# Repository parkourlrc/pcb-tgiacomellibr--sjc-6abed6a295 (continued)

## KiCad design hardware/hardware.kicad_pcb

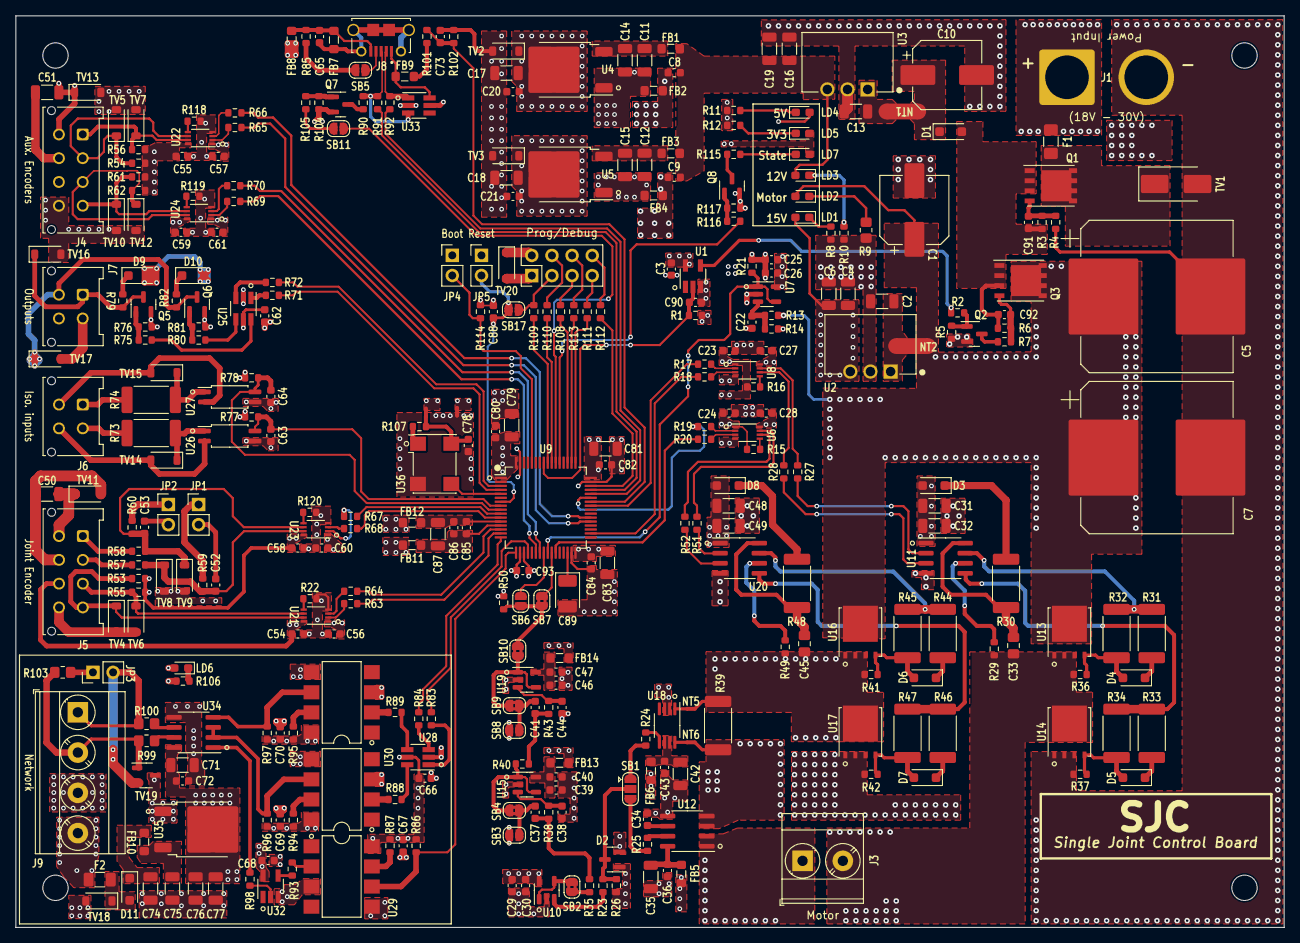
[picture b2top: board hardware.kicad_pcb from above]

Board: 4 copper layers, 160.0 x 115.0 mm, 346 parts (0 on the bottom side), 216 nets.

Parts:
C1, C10: 47uF 63V 20%; CP_Elec_8x10.5
C2, C6, C11, C12, C13, C17, C18, C19, C31, C35, C42, C48, C75, C76, C79: 10uF 10% 50V; C_1206_3216Metric
C3, C8, C9, C20, C21, C23, C24, C25, C27, C28, C29, C36, C39, C43, C46, C54, C55, C56, C57, C58, C59, C60, C61, C62, C65, C66, C67, C68, C69, C70, C72, C73, C78, C80, C82, C84, C86, C88, C93: 100nF 5% 50V; C_0603_1608Metric
C4, C16: 22uF 10% 25V; C_1206_3216Metric
C5, C7: 680uF 63V 20%; CP_Elec_18x17.5
C14, C15, C32, C49, C50, C51, C71, C74, C77, C81, C83, C87: 1uF 10% 50V; C_1206_3216Metric
C22: 12nF 5% 50V; C_0603_1608Metric
C26, C30, C40, C47, C63, C64, C85, C90, C91, C92: 10nF 5% 50V; C_0603_1608Metric
C33, C45: 82nF 5% 50V; C_0805_2012Metric_Pad1.18x1.45mm_HandSolder
C34, C52, C53: 22nF 5% 50V; C_0603_1608Metric
C37, C38, C41, C44: 39nF 5% 50V; C_0603_1608Metric
C89: 4.7uF 10% 20V; CP_EIA-3528-15_AVX-H_Pad1.50x2.35mm_HandSolder
D1, D3, D8, D11: PMEG60T20ELR; D_SOD-123F
D2: BAT54S; SOT-23
D4, D5, D6, D7, D9, D10: PMEG60T10ELR; D_SOD-123F
F1: 25A 32V; Fuse_1206_3216Metric_Pad1.42x1.75mm_HandSolder
F2: 60V 100mA; Fuse_1206_3216Metric
FB1, FB2, FB3, FB4, FB5, FB6, FB7, FB8, FB9, FB10, FB11, FB12, FB13, FB14: 220R 3A; L_0805_2012Metric_Pad1.05x1.20mm_HandSolder
H1, H2, H3, H4: MountingHole; MountingHole_3.2mm_M3_ISO7380
J1: V_{POWER}; SolderWire-16.8sqmm_1x02_P10.0mm_D5.5mm_OD7.0mm
J3: Motor; TerminalBlock_Phoenix_MKDS-3-2-5.08_1x02_P5.08mm_Horizontal
J4: Aux. encoders; Molex_Micro-Fit_3.0_43045-0812_2x04_P3.00mm_Vertical
J5: Joint encoders; Molex_Micro-Fit_3.0_43045-0812_2x04_P3.00mm_Vertical
J6: Isolated Inputs; Molex_Micro-Fit_3.0_43045-0412_2x02_P3.00mm_Vertical
J7: Outputs; Molex_Micro-Fit_3.0_43045-0412_2x02_P3.00mm_Vertical
J8: AMPHENOL_10118194-0001LF
J9: RS-485; TerminalBlock_Phoenix_MKDS-3-4-5.08_1x04_P5.08mm_Horizontal
J10: PROG_{DBG}; PinHeader_2x04_P2.54mm_Vertical
JP1, JP2, JP4, JP5: E-STOP_DIV; PinHeader_1x02_P2.54mm_Vertical
JP3: RS-485 TERM; PinHeader_1x02_P2.54mm_Vertical
LD1, LD2, LD3, LD4, LD5, LD6, LD7: 1.8V @ 5mA; LED_0603_1608Metric_Pad1.05x0.95mm_HandSolder
NT1, NT2: PWR-DRV; NetTie-2_SMD_Pad2.0mm
NT3: 3V3_OSC; NetTie-2_SMD_Pad0.5mm
NT4: GND_OSC; NetTie-2_SMD_Pad0.5mm
NT5: SHUNT IN-; NetTie-2_SMD_Pad0.5mm
NT6: SHUNT IN+; NetTie-2_SMD_Pad0.5mm
Q1, Q3: SI7149ADP; PowerPAK_SO-8_Single
Q2, Q5, Q6, Q8: NDS7002A; SOT-23
Q7: BSS84; SOT-23
R1, R3, R5, R6, R13, R36, R37, R41, R42, R76, R81, R85, R104, R114, R117: 100k 1%; R_0603_1608Metric
R2, R21, R59, R60, R75, R80, R86, R96, R97, R105, R116: 1k 1%; R_0603_1608Metric
R4, R7, R102: 82k 0.1%; R_0603_1608Metric
R8, R15, R16, R22, R53, R54, R55, R56, R61, R62, R87, R94, R95, R118, R119, R120: 2k7 1%; R_0603_1608Metric
R9: 5.62k 5% 250mW; R_0805_2012Metric_Pad1.20x1.40mm_HandSolder
R10, R77, R78, R79, R82: 2k 5%; R_0603_1608Metric
R11: 680R 1%; R_0603_1608Metric
R12, R106, R115: 330R 1%; R_0603_1608Metric
R14, R23, R107: 10k 1%; R_0603_1608Metric
R17, R18, R19, R20, R27, R28, R51, R52, R63, R64, R65, R66, R67, R68, R69, R70, R71, R72, R83, R84, R98, R108, R109, R110, R111, R112, R113: 33R 1%; R_0603_1608Metric
R24: 270R 0.1%; R_0603_1608Metric
R25: 510R 0.1%; R_0603_1608Metric
R26, R35, R38, R40, R43, R50: 1.02k 0.1%; R_0603_1608Metric
R29, R49: 0R; R_0603_1608Metric
R30, R48: 2R 5% 2W; R_2512_6332Metric_Pad1.40x3.35mm_HandSolder
R31, R33, R44, R46: 2.4R 1% 1W; R_2512_6332Metric_Pad1.40x3.35mm_HandSolder
R32, R34, R45, R47: 130R 1% 1W; R_2512_6332Metric_Pad1.40x3.35mm_HandSolder
R39: 8mR 1% 2W; R_2512_6332Metric_Pad1.40x3.35mm_HandSolder
R57, R58, R90: 1.5k 1%; R_0603_1608Metric
R73, R74: 1.6k 5% 1W; R_2512_6332Metric_Pad1.40x3.35mm_HandSolder
R88, R89, R93: 160R 5% 1/8W; R_0603_1608Metric
R91, R92: 22R 1%; R_0603_1608Metric
R99, R100: 10R 1% 1/2W; R_0805_2012Metric_Pad1.20x1.40mm_HandSolder
R101: 47k 0.1%; R_0603_1608Metric
R103: 120R 0.1% 1/8W; R_0805_2012Metric_Pad1.20x1.40mm_HandSolder
SB1: CS_SEL; SolderJumper-3_P1.3mm_Open_RoundedPad1.0x1.5mm
SB2, SB4, SB7, SB9, SB10: SolderJumper-2_P1.3mm_Bridged2Bar_RoundedPad1.0x1.5mm
SB3, SB5, SB6, SB8, SB11, SB17: SolderJumper-2_P1.3mm_Open_RoundedPad1.0x1.5mm
TV1: SMBJ30A; D_SMB_Handsoldering
TV2, TV5, TV7, TV8, TV9, TV10, TV12, TV13: PTVS5V0S1UR; D_SOD-123
TV3, TV20: PTVS3V3S1UR; D_SOD-123
TV4, TV6, TV11, TV16, TV17, TV18: PTVS12VS1UR; D_SOD-123
TV14, TV15: PTVS30VS1UR; D_SOD-123
TV19: SM712; SOT-23-3
U1, U32: SN74LVC1G04DBVR; SOT-23-5_HandSoldering
U2: VXO78015-1000; CONV_VXO78015-1000
U3: VXO78012-1000; CONV_VXO78012-1000
U4: NCP1117DT50; TO-252-2
U5, U35: NCP1117DT33; TO-252-2
U6, U8, U21, U22, U23, U24: 74LVC2T45DC; VSSOP-8_2.3x2mm_P0.5mm
U7, U10, U15, U19: TLV9051; SOT-23-5
U9: STM32F446RETx; LQFP-64_10x10mm_P0.5mm
U11, U20: FAN7382; SOIC-8_3.9x4.9mm_P1.27mm
U12: ACS712-20A; SOIC-8_3.9x4.9mm_P1.27mm
U13, U14, U16, U17: BSC0902NSI; TDSON-8-1
U18: AD8418; MSOP-8_3x3mm_P0.65mm
U25, U28: SN74LVC2G04; SOT-23-6_Handsoldering
U26, U27: TLP291; SOP-4_4.4x2.6mm_P1.27mm
U29, U30, U31: 6N137; SMDIP-8_W7.62mm
U33: USBLC6-4SC6; SOT-23-6_Handsoldering
U34: SN65HVD75DR; SOIC-8_3.9x4.9mm_P1.27mm
U36: YSO110TR-16MHz; Oscillator_SMD_YXC_YSO110TR_7050-4Pin_7.0x5.0mm

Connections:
+3V3: C3.1, C18.2, C21.2, C23.2, C24.2, C25.1, C26.1, C29.1, C30.1, C56.1, C57.1, C60.2, C61.1, C62.1, C66.1, C67.1, C79.2, C80.2, C81.2, C82.2, C83.2, C84.2, C93.2, D2.2, FB11.1, FB13.2, FB14.2, J10.2, JP4.1, LD5.2 (A), LD7.2 (A), NT3.2, Q7.2 (S), R1.2, R15.2, R16.2, R77.2, R78.2, R86.2, R87.2, R104.2, TV3.1 (K), TV20.1 (K), U1.5 (VCC), U5.2 (VO), U6.1 (VCCA), U7.5 (V+), U8.1 (VCCA), U9.1 (VBAT), U9.19 (VDD), U9.32 (VDD), U9.48 (VDD), U9.64 (VDD), U10.5 (V+), U21.1 (VCCA), U22.1 (VCCA), U23.1 (VCCA), U24.1 (VCCA), U25.5 (V_{CC}), U28.5 (V_{CC}), U29.8 (VCC)
+3V3A: C85.2, C86.2, C87.2, FB11.2, U9.13 (VDDA)
+3V3_ISO: C68.1, C69.1, C70.1, C71.1, C72.1, C76.2, C77.2, LD6.2 (A), R94.2, R95.2, R96.2, R97.2, U30.8 (VCC), U31.8 (VCC), U32.5 (VCC), U34.8 (VCC), U35.2 (VO)
+3V3_OSC: C78.1, NT3.1, R107.2, U36.4 (V_{DD})
+5V: C17.2, C20.2, C27.1, C28.1, C50.2, C51.2, C54.2, C55.2, C58.1, C59.2, D9.2 (A), D10.2 (A), FB5.1, FB6.1, J4.5, J4.7, J5.5, J5.7, LD4.2 (A), R53.2, R54.2, R55.2, R56.2, R61.2, R62.2, TV2.1 (K), TV11.1 (K), TV13.1 (K), U4.2 (VO), U6.8 (VCCB), U8.8 (VCCB), U21.8 (VCCB), U22.8 (VCCB), U23.8 (VCCB), U24.8 (VCCB), U33.5 (VBUS)
+5V_USB: FB9.2, J8.1 (VBUS), U33.6 (I/O4)
+12V: C8.2, C9.2, C16.2, C19.2, FB1.2, FB3.1, LD3.2 (A), U3.3 (+V_{OUT})
+12V_ISO: F2.1, J9.4
+15V: C4.2, C6.2, C31.1, C32.1, C48.2, C49.2, D3.2 (A), D8.2 (A), LD1.2 (A), U2.3 (+V_{OUT}), U11.1 (V_{CC}), U20.1 (V_{CC})
/Communication/+12V_ISO_DC: C74.2, D11.1 (K), FB10.2
/Communication/+12V_ISO_FLT: C75.2, FB10.1, U35.3 (VI)
/Communication/COM_USB_D+: R91.1, U9.45 (PA12)
/Communication/COM_USB_D-: R92.1, U9.44 (PA11)
/Communication/COM_USB_PU: SB11.1 (A), U9.54 (PD2)
/Communication/COM_USB_V_{BUS}_SIG: C73.2, R101.2, R102.2, U9.42 (PA9)
/Communication/ISO_RX: R98.2, U32.2 (A)
/Communication/ISO_TX: R97.1, U31.6 (VO), U34.4 (D)
/Communication/ISO_~RE_DE: R96.1, U30.6 (VO), U34.2 (~RE), U34.3 (DE)
/Communication/RS485+: J9.2, R99.1, R103.1, TV19.1
/Communication/RS485-: J9.1, JP3.2, R100.1, TV19.2
/Communication/RS485_RX: R86.1, U9.17 (PA3), U29.6 (VO)
/Communication/RS485_TX: R84.2, U9.16 (PA2)
/Communication/RS485_~RE_DE: R83.2, U9.20 (PA4)
/Communication/RS+: R99.2, U34.7 (B)
/Communication/RS-: R100.2, U34.6 (A)
/Communication/USB_D+: J8.3 (D+), R90.1, R91.2, U33.3 (I/O2)
/Communication/USB_D-: J8.2 (D-), R92.2, U33.1 (I/O1)
/Communication/USB_DP_PU: Q7.3 (D), R90.2
/Control/AUX1_ENC_CH1: R69.1, U9.22 (PA6)
/Control/AUX1_ENC_CH2: R70.1, U9.23 (PA7)
/Control/AUX2_ENC_CH1: R65.1, U9.37 (PC6)
/Control/AUX2_ENC_CH2: R66.1, U9.38 (PC7)
/Control/BOOT: JP4.2, R114.2, U9.60 (BOOT0)
/Control/CURRENT_SIGNAL_FILT: R50.2, SB6.2 (B), SB7.2 (B), SB10.2 (B)
/Control/DEBUG_USART_TX: R108.1, U9.51 (PC10)
/Control/GP_ISO_IN_A: C63.2, R77.1, U9.8 (PC0), U26.4
/Control/GP_ISO_IN_B: C64.2, R78.1, U9.9 (PC1), U27.4
/Control/GP_OUT_A: R71.2, U9.4 (PC15)
/Control/GP_OUT_B: R72.2, U9.3 (PC14)
/Control/JOINT_ENC_CH1: R64.1, U9.14 (PA0)
/Control/JOINT_ENC_CH2: R63.1, U9.15 (PA1)
/Control/JOINT_SW_L: R67.1, U9.10 (PC2)
/Control/JOINT_SW_R: R68.1, U9.11 (PC3)
/Control/JTCK/SWCLK: R111.1, U9.49 (PA14)
/Control/JTDI: R113.1, U9.50 (PA15)
/Control/JTDO/TRACESWO: R110.1, U9.55 (PB3)
/Control/JTMS/SWDIO: R112.1, U9.46 (PA13)
/Control/L_MOT_HI_{PWM}: R17.2, U9.41 (PA8)
/Control/L_MOT_LO_{PWM}: R18.2, U9.34 (PB13)
/Control/MCU_OSC: U9.5 (PH0), U36.3 (OUT)
/Control/MOTOR_INPUT_VOLTAGE_SIG: R21.2, U7.1, U7.4 (-), U9.25 (PC5)
/Control/NJTRST: R109.1, U9.56 (PB4)
/Control/NRST: C88.2, JP5.2, SB17.2 (B), U9.7 (NRST)
/Control/R_MOT_HI_{PWM}: R19.2, U9.43 (PA10)
/Control/R_MOT_LO_{PWM}: R20.2, U9.27 (PB1)
/Control/SYS_HEARTBEAT: R116.2, U9.53 (PC12)
/Control/V_{MOTOR}_~EN: C90.2, R1.1, U1.2 (A), U9.57 (PB5)
/Encoders/JNT_ENC_A: J5.3, R55.1, TV6.1 (K), U21.6 (2B)
/Encoders/JNT_ENC_B: J5.4, R53.1, TV4.1 (K), U21.7 (1B)
/Encoders/JNT_ESTOP_A: J5.2, R57.1
/Encoders/JNT_ESTOP_B: J5.1, R58.1
/Encoders/JNT_SW_A: C52.2, R57.2, R59.2, TV8.1 (K), U23.7 (1B)
/Encoders/JNT_SW_B: C53.2, R58.2, R60.2, TV9.1 (K), U23.6 (2B)
/Encoders/S1_ENC_A: J4.3, R62.1, TV12.1 (K), U24.7 (1B)
/Encoders/S1_ENC_B: J4.4, R61.1, TV10.1 (K), U24.6 (2B)
/Encoders/S2_ENC_A: J4.1, R56.1, TV7.1 (K), U22.7 (1B)
/Encoders/S2_ENC_B: J4.2, R54.1, TV5.1 (K), U22.6 (2B)
/GPIOs/ISO_IN_A: J6.2, R73.2
/GPIOs/ISO_IN_A_{COM}: J6.4, TV14.2 (A), U26.2
/GPIOs/ISO_IN_B: J6.1, R74.2
/GPIOs/ISO_IN_B_{COM}: J6.3, TV15.2 (A), U27.2
/GPIOs/OUT_A: J7.1, Q5.3 (D), R79.1, TV16.1 (K)
/GPIOs/OUT_B: J7.3, Q6.3 (D), R82.1, TV17.1 (K)
/Motor/CS_MEAS: R23.2, U10.3 (+)
/Motor/CS_MEAS_ACS712: R25.1, U12.7 (VIOUT)
/Motor/CS_MEAS_AD8418: R24.1, U18.5 (OUT)
/Motor/CS_MEAS_PRE_FILT: SB2.1 (A), U10.1, U10.4 (-)
/Motor/DC_MOT_T1: C33.1, J3.2, R29.2, R36.1, U13.1 (S), U13.2 (S), U13.3 (S), U14.5 (D)
/Motor/DC_MOT_T1_RET: J3.1, U12.1 (IP+), U12.2 (IP+)
/Motor/DC_MOT_T1_SHUNT: NT6.1, R39.1, U12.3 (IP-), U12.4 (IP-)
/Motor/DC_MOT_T2: C45.1, NT5.1, R39.2, R41.1, R49.2, U16.1 (S), U16.2 (S), U16.3 (S), U17.5 (D)
/Motor/L_HSG: D4.2 (A), R32.1, R36.2, U13.4 (G)
/Motor/L_PWM: R27.2, U8.7 (1B)
/Motor/R_HSG: D6.2 (A), R41.2, R45.1, U16.4 (G)
/Motor/R_PWM: R51.2, U6.7 (1B)
/Motor/~L_PWM: R28.2, U8.6 (2B)
/Motor/~R_PWM: R52.2, U6.6 (2B)
/Power Supply/15V_REG_IN: C2.2, NT2.2, U2.1 (+V_{IN})
GND: C3.2, C11.1, C12.1, C14.1, C15.1, C17.1, C18.1, C20.1, C21.1, C22.1, C23.1, C24.1, C25.2, C26.2, C27.2, C28.2, C29.2, C30.2, C34.1, C35.2, C36.2, C38.1, C39.2, C40.2, C42.2, C43.2, C44.1, C46.2, C47.2, C50.1, C51.1, C52.1, C53.1, C54.1, C55.1, C56.2, C57.2, C58.2, C59.1, C60.1, C61.2, C62.2, C63.1, C64.1, C66.2, C67.2, C73.1, C79.1, C80.1, C81.1, C82.1, C83.1, C84.1, C88.1, C89.2, C90.1, C93.1, D2.1, FB2.1, FB4.1, FB8.1, FB12.1, J4.6, J4.8, J5.6, J5.8, J7.2, J7.4, J10.1, JP1.2, JP2.2, JP5.1, NT4.2, Q5.2 (S), Q6.2 (S), Q8.2 (S), R11.2, R12.2, R14.1, R21.1, R22.1, R26.1, R50.1, R76.1, R81.1, R102.1, R114.1, R117.1, R118.1, R119.1, R120.1, SB3.2 (B), SB8.2 (B), TV2.2 (A), TV3.2 (A), TV4.2 (A), TV5.2 (A), TV6.2 (A), TV7.2 (A), TV8.2 (A), TV9.2 (A), TV10.2 (A), TV11.2 (A), TV12.2 (A), TV13.2 (A), TV16.2 (A), TV17.2 (A), TV20.2 (A), U1.3 (GND), U4.1 (GND), U5.1 (GND), U6.4 (GND), U7.2 (V-), U8.4 (GND), U9.18 (VSS), U9.31 (VSS), U9.47 (VSS), U9.63 (VSS), U10.2 (V-), U12.5 (GND), U15.2 (V-), U18.2 (GND), U18.3 (REF2), U19.2 (V-), U21.4 (GND), U22.4 (GND), U23.4 (GND), U24.4 (GND), U25.2 (GND), U26.3, U27.3, U28.2 (GND), U29.5 (GND), U30.3 (C), U31.3 (C), U33.2 (GND)
GNDA: C85.1, C86.1, C87.1, FB12.2, U9.12 (VSSA)
GND_ISO: C68.2, C69.2, C70.2, C71.2, C72.2, C74.1, C75.1, C76.1, C77.1, J9.3, R106.2, TV18.2 (A), TV19.3, U29.3 (C), U30.5 (GND), U31.5 (GND), U32.3 (GND), U34.5 (GND), U35.1 (GND)
GND_OSC: C78.2, NT4.1, U36.2 (GND)
GND_USB: C65.1, FB7.2, FB8.2, J8.5 (GND), R85.1
unnamed: C37.2, R35.2, R38.1
unnamed: C41.2, R40.2, R43.1
unnamed: C65.2, FB7.1, J8.S1 (Shield), J8.S2 (Shield), J8.S3 (Shield), J8.S4 (Shield), J8.S5 (Shield), J8.S6 (Shield)
unnamed: C10.1, D1.1 (K), NT1.1
unnamed: D3.1 (K), R30.2
unnamed: D4.1 (K), R31.1
unnamed: D5.2 (A), R34.1, R37.2, U14.4 (G)
unnamed: D5.1 (K), R33.1
unnamed: D6.1 (K), R44.1
unnamed: D7.2 (A), R42.2, R47.1, U17.4 (G)
unnamed: D7.1 (K), R46.1
unnamed: D8.1 (K), R48.2
unnamed: D9.1 (K), R79.2
unnamed: D10.1 (K), R82.2
unnamed: D11.2 (A), F2.2, TV18.1 (K)
unnamed: FB9.1, R101.1
unnamed: J8.4 (ID), SB5.1 (A)
unnamed: J10.3, R109.2, SB17.1 (A)
unnamed: J10.4, R110.2
unnamed: J10.5, R108.2
unnamed: J10.6, R113.2
unnamed: J10.7, R111.2
unnamed: J10.8, R112.2
unnamed: JP1.1, R59.1
unnamed: JP2.1, R60.1
unnamed: JP3.1, R103.2
unnamed: LD1.1 (K), R8.1
unnamed: LD2.1 (K), R9.1
unnamed: LD3.1 (K), R10.1
unnamed: LD4.1 (K), R11.1
unnamed: LD5.1 (K), R12.1
unnamed: LD6.1 (K), R106.1
unnamed: LD7.1 (K), R115.1
unnamed: C91.1, Q1.4 (G), R3.1, R4.2
unnamed: Q2.3 (D), R7.1
unnamed: Q2.1 (G), R2.1, R5.2
unnamed: C92.1, Q3.4 (G), R6.1, R7.2
unnamed: Q5.1 (G), R75.1, R76.2
unnamed: Q6.1 (G), R80.1, R81.2
unnamed: Q7.1 (G), R104.1, R105.2
unnamed: Q8.3 (D), R115.2
unnamed: Q8.1 (G), R116.1, R117.2
unnamed: R24.2, SB1.1 (A)
unnamed: R25.2, SB1.3 (B)
unnamed: D2.3, R23.1, R26.2, SB1.2 (C)
unnamed: R35.1, SB2.2 (B)
unnamed: C37.1, SB3.1 (A), SB4.1 (A)
unnamed: R40.1, SB4.2 (B), U15.1, U15.4 (-)
unnamed: R85.2, SB5.2 (B)
unnamed: SB6.1 (A), U9.24 (PC4)
unnamed: SB7.1 (A), U9.26 (PB0)
unnamed: C41.1, SB8.1 (A), SB9.1 (A)
unnamed: SB9.2 (B), SB10.1 (A), U19.1, U19.4 (-)
unnamed: R105.1, SB11.2 (B)
unnamed: R73.1, TV14.1 (K), U26.1
unnamed: R74.1, TV15.1 (K), U27.1
unnamed: R2.2, U1.4 (Y)
unnamed: C13.2, NT1.2, U3.1 (+V_{IN})
unnamed: C11.2, C14.2, FB1.1, U4.3 (VI)
unnamed: C12.2, C15.2, FB3.2, U5.3 (VI)
unnamed: R19.1, U6.2 (1A)
unnamed: R20.1, U6.3 (2A)
unnamed: R15.1, U6.5 (DIR)
unnamed: C22.2, R13.1, R14.2, U7.3 (+)
unnamed: R17.1, U8.2 (1A)
unnamed: R18.1, U8.3 (2A)
unnamed: R16.1, U8.5 (DIR)
unnamed: C89.1, U9.30 (VCAP_1)
unnamed: R27.1, U11.2 (H_{IN})
unnamed: R31.2, R32.2, U11.7 (H_{O})
unnamed: R28.1, U11.3 (L_{IN})
unnamed: R33.2, R34.2, U11.5 (L_{O})
unnamed: C33.2, R30.1, U11.8 (V_{B})
unnamed: R29.1, U11.6 (V_{S})
unnamed: C34.2, U12.6 (FILTER)
unnamed: C35.1, C36.1, FB5.2, U12.8 (VCC)
unnamed: C38.2, R38.2, U15.3 (+)
unnamed: C39.1, C40.1, FB13.1, U15.5 (V+)
unnamed: NT6.2, U18.8 (IN+)
unnamed: NT5.2, U18.1 (IN-)
unnamed: C42.1, C43.1, FB6.2, U18.6 (VS), U18.7 (REF1)
unnamed: C44.2, R43.2, U19.3 (+)
unnamed: C46.1, C47.1, FB14.1, U19.5 (V+)
unnamed: R51.1, U20.2 (H_{IN})
unnamed: R44.2, R45.2, U20.7 (H_{O})
unnamed: R52.1, U20.3 (L_{IN})
unnamed: R46.2, R47.2, U20.5 (L_{O})
unnamed: C45.2, R48.1, U20.8 (V_{B})
unnamed: R49.1, U20.6 (V_{S})
unnamed: R63.2, U21.2 (1A)
unnamed: R64.2, U21.3 (2A)
unnamed: R22.2, U21.5 (DIR)
unnamed: R65.2, U22.2 (1A)
unnamed: R66.2, U22.3 (2A)
unnamed: R118.2, U22.5 (DIR)
unnamed: R67.2, U23.2 (1A)
unnamed: R68.2, U23.3 (2A)
unnamed: R120.2, U23.5 (DIR)
unnamed: R69.2, U24.2 (1A)
unnamed: R70.2, U24.3 (2A)
unnamed: R119.2, U24.5 (DIR)
unnamed: R71.1, U25.1 (1A)
unnamed: R75.2, U25.6 (1Y)
unnamed: R72.1, U25.3 (2A)
unnamed: R80.2, U25.4 (2Y)
unnamed: R83.1, U28.1 (1A)
unnamed: R88.1, U28.6 (1Y)
unnamed: R84.1, U28.3 (2A)
unnamed: R89.1, U28.4 (2Y)
unnamed: R93.1, U29.2 (A)
unnamed: R87.1, U29.7 (EN)
unnamed: R88.2, U30.2 (A)
unnamed: R94.1, U30.7 (EN)
unnamed: R89.2, U31.2 (A)
unnamed: R95.1, U31.7 (EN)
unnamed: R93.2, U32.4 (Y)
unnamed: R98.1, U34.1 (R)
unnamed: R107.1, U36.1 (En)
PGND: C1.2, C2.1, C4.1, C5.2, C6.1, C7.2, C8.1, C9.1, C10.2, C13.1, C16.1, C19.1, C31.2, C32.2, C48.1, C49.1, FB2.2, FB4.2, J1.2, Q2.2 (S), R4.1, R5.1, R8.2, R9.2, R10.2, R37.1, R42.1, TV1.2 (A), U2.2 (GND), U3.2 (GND), U11.4 (Com), U14.1 (S), U14.2 (S), U14.3 (S), U17.1 (S), U17.2 (S), U17.3 (S), U20.4 (Com)
V_{DC}+: C91.2, C92.2, D1.2 (A), Q1.1 (S), Q1.2 (S), Q1.3 (S), Q3.1 (S), Q3.2 (S), Q3.3 (S), R3.2, R6.2
V_{MOTOR}: C1.1, C5.1, C7.1, LD2.2 (A), NT2.1, Q3.5 (D), R13.2, U13.5 (D), U16.5 (D)
V_{PWR}+: F1.1, J1.1
V_{PWR}_Fuse+: F1.2, Q1.5 (D), TV1.1 (K)

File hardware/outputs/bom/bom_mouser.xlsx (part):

Comment | Designator | Footprint | Quantity Per PCB | LCSC part number | MF | PN | Mouser #
Capacitor, 100nF, ±5%, X7R, 50V, SMD 0603 | C3 C8 C9 C20 C21 C23 C24 C25 C27 C28 C29 C36 C39 C43 C46 C54 C55 C56 C57 C58 C5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 | C_0603_1608Metric | 39 | C91183 | YAGEO | CC0603JRX7R9BB104
Capacitor, 10nF, ±5%, NP0, 50V, SMD 0603 | C26 C30 C40 C47 C63 C64 C85 C90 C91 C92 | C_0603_1608Metric | 10 | C389113 | YAGEO | CC0603JRNPO9BN103
Capacitor, 10uF, ±10%, X5R, 50V, SMD 1206 | C2 C6 C11 C12 C13 C17 C18 C19 C31 C35 C42 C48 C75 C76 C79 | C_1206_3216Metric | 15 | C13585 | Samsung Electro-Mechanics | CL31A106KBHNNNE
Capacitor, 12nF, ±5%, X7R, 50V, SMD 0603 | C22 | C_0603_1608Metric | 1 | C302013 | Walsin Tech Corp | 0603B123J500CT
Capacitor, 1uF, ±10%, X7R, 50V, SMD 1206 | C14 C15 C32 C49 C50 C51 C71 C74 C77 C81 C83 C87 | C_1206_3216Metric | 12 | C1848 | Samsung Electro-Mechanics | CL31B105KBHNNNE
Capacitor, 22nF, ±5%, X7R, 50V, SMD 0603 | C34 C52 C53 | C_0603_1608Metric | 3 | C277528 | YAGEO | CC0603JRX7R9BB223
Capacitor, 22uF, ±10%, X5R, 25V, SMD 1206 | C4 C16 | C_1206_3216Metric | 2 | C105213 | Walsin Tech Corp | 1206X226K250CT
Capacitor, 39nF, ±5%, X7R, 50V, SMD 0603 | C37 C38 C41 C44 | C_0603_1608Metric | 4 | C519553 | YAGEO | CC0603JRX7R9BB393
Tantalum Capacitor, 4.7uF, ±10%, X5R, 50V, SMD 1206 | C89 | CP_EIA-3528-15_AVX-H_Pad1.50x2.35mm_HandSolder | 1 | C308921 | Kyocera AVX | TPSB475K020R0750
Electrolytic capacitor, 47uF, 20%, 63V, SMD D8xL10.5mm | C1 C10 | CP_Elec_8x10.5 | 2 | C116428 | ST(Semtech) | CS1J470M-CRF10
Electrolytic capacitor, 680uF, 20%, 63V, SMD D18xL16.5mm | C5 C7 | CP_Elec_18x17.5 | 2 | C249956 | Lelon | VZH681M1JTR-1816
Capacitor, 82nF, ±5%, X7R, 50V, SMD 0805 | C33 C45 | C_0805_2012Metric_Pad1.18x1.45mm_HandSolder | 2 | C520047 | YAGEO | CC0805JRX7R9BB823
Dual Series Schottky Barrier Diodes, 30V Reverse Voltage, 200mA Forward Current | D2 | SOT-23 | 1 | C19726 | Onsemi | BAT54SLT1G
Schottky diode, 60 V reverse voltage, 1 A average forward current, 600 mV forwa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 | D4 D5 D6 D7 D9 D10 | D_SOD-123F | 6 | C552945 | Nexperia | PMEG60T10ELRX
60V, 2A low leakage current Trench MEGA Schottky barrier rectifier, SOD-123W | D1 D3 D8 D11 | D_SOD-123F | 4 | C552947 | Nexperia | PMEG60T20ELRX
Ferrite Bead, 3A, 40mΩ DC Resistance, 220Ω@100MHz, SMD 0805 | FB1 FB2 FB3 FB4 FB5 FB6 FB7 FB8 FB9 FB10 FB11 FB12 FB13 FB14 | L_0805_2012Metric_Pad1.05x1.20mm_HandSolder | 14 | C76818 | TDK | MPZ2012S221AT000
USB Micro Type B connector | J8 | AMPHENOL_10118194-0001LF | 1 | C132563 | Amphenol ICC | 10118194-0001LF
Generic connector, double row, 02x04, top/bottom pin numbering scheme (row 1: 1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 | J4 J5 | Molex_Micro-Fit_3.0_43045-0812_2x04_P3.00mm_Vertical | 2
Generic connector, double row, 02x02, top/bottom pin numbering scheme (row 1: 1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 | J6 J7 | Molex_Micro-Fit_3.0_43045-0412_2x02_P3.00mm_Vertical | 2
Generic screw terminal, single row, 01x02, script generated (kicad-library-util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 | J3 | TerminalBlock_Phoenix_MKDS-3-2-5.08_1x02_P5.08mm_Horizontal | 1 | C8465 | Ningbo Kangnex Elec | WJ500V-5.08-2P
Generic connector, single row, 01x04, script generated (kicad-library-utils/sch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 | J9 | TerminalBlock_Phoenix_MKDS-3-4-5.08_1x04_P5.08mm_Horizontal | 1 | C2915641 | DIBO | DB128V-5.08-4P-GN-S
2 Pos. Pin Header, 2.54 mm Pitch | JP1 JP2 JP3 JP4 JP5 | PinHeader_1x02_P2.54mm_Vertical | 5 | C234182 | MOLEX | 22284020
Light emitting diode | LD1 LD2 LD3 LD4 LD5 LD6 LD7 | LED_0603_1608Metric_Pad1.05x0.95mm_HandSolder | 7 | C165982 | BrtLed (Bright LED Elec) | BL-HGE36G-AV-TRB
-0.13A Id, -50V Vds, P-Channel MOSFET, SOT-23 | Q7 | SOT-23 | 1 | C85202 | Diodes Incorporated | BSS84-7-F
280mA Id, 60V Vds, 20V Vgss, N-Channel MOSFET, SOT-23 | Q2 Q5 Q6 Q8 | SOT-23 | 4 | C74715 | onsemi | NDS7002A
50A Id, -30 V Drain-Source Voltage, 25 V Gate-Source Voltage, 5.2 mOhm Ron, Pow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 | Q1 Q3 | PowerPAK_SO-8_Single | 2 | C554002 | Vishay Intertech | SI7149ADP-T1-GE3
Resistor, 0 Ohms, ±5%, 1/10W, SMD 0603 | R29 R49 | R_0603_1608Metric | 2 | C103196 | RALEC | RTT03000JTP
Resistor, 1.6 kOhms, ±5%, 1W, SMD 2512 | R73 R74 | R_2512_6332Metric_Pad1.40x3.35mm_HandSolder | 2 | C453392 | FH (Guangdong Fenghua Advanced Tech) | RC-12K162JT
Resistor, 1.02 kOhms, ±0.1%, 1/10W, SMD 0603 | R26 R35 R38 R40 R43 R50 | R_0603_1608Metric | 6 | C705819 | YAGEO | RT0603BRE071K02L
Resistor, 1.5 kOhms, ±1%, 1/10W, SMD 0603 | R57 R58 R90 | R_0603_1608Metric | 3 | C285210 | Viking Tech | CR-03FA7---1K5
Resistor, 100k Ohms, ±1%, 1/10W, SMD 0603 | R1 R3 R5 R6 R13 R36 R37 R41 R42 R76 R81 R85 R104 R114 R117 | R_0603_1608Metric | 15 | C14675 | YAGEO | RC0603FR-07100KL
Pulse-Proof/Anti-Surge Resistor, 10 Ohms, ±1%, 1/2W, SMD 0805 | R99 R100 | R_0805_2012Metric_Pad1.20x1.40mm_HandSolder | 2 | C441969 | PANASONIC | ERJP06F10R0V
Resistor, 10 kOhms, ±1%, 1/10W, SMD 0603 | R14 R23 R107 | R_0603_1608Metric | 3 | C98220 | YAGEO | RC0603FR-0710KL
Resistor, 120 Ohms, ±0.1%, 1/8W, SMD 0805 | R103 | R_0805_2012Metric_Pad1.20x1.40mm_HandSolder | 1 | C2828708 | Viking Tech | ARG05BTC1200
Resistor, 130 Ohms, ±1%, 1W, SMD 2512 | R32 R34 R45 R47 | R_2512_6332Metric_Pad1.40x3.35mm_HandSolder | 4 | C728111 | YAGEO | AC2512FK-07130RL
Resistor, 160 Ohms, ±5%, 1/8W, SMD 0603 | R88 R89 R93 | R_0603_1608Metric | 3 | C171721 | KOA Speer Elec | RK73B1JTTD161J
Resistor, 1.0 kOhms, ±1%, 1/10W, SMD 0603 | R2 R21 R59 R60 R75 R80 R86 R96 R97 R105 R116 | R_0603_1608Metric | 11 | C22548 | YAGEO | RC0603FR-071KL
Resistor, 2.4 Ohms, ±1%, 1W, SMD 2512 | R31 R33 R44 R46 | R_2512_6332Metric_Pad1.40x3.35mm_HandSolder | 4 | C175225 | Ever Ohms Tech | CR2512F2R40E04S
Resistor, 22 Ohms, ±1%, 1/10W, SMD 0603 | R91 R92 | R_0603_1608Metric | 2 | C107701 | YAGEO | RC0603FR-0722RL
Resistor, 270 Ohms, ±0.1%, 1/10W, SMD 0603 | R24 | R_0603_1608Metric | 1 | C861270 | YAGEO | RT0603BRD07270RL
Resistor, 2 Ohms, ±5%, 2W, SMD 2512 | R30 R48 | R_2512_6332Metric_Pad1.40x3.35mm_HandSolder | 2 | C91926 | Ever Ohms Tech | CRH2512J2R00E04S
Resistor, 2k Ohms, ±5%, 1/10W, SMD 0603 | R10 R77 R78 R79 R82 | R_0603_1608Metric | 5 | C103396 | RALEC | RTT03202JTP
Resistor, 2.7 kOhms, ±1%, 1/10W, SMD 0603 | R8 R15 R16 R22 R53 R54 R55 R56 R61 R62 R87 R94 R95 R118 R119 R120 | R_0603_1608Metric | 16 | C114612 | YAGEO | RC0603FR-072K7L
Resistor, 330 Ohms, ±1%, 1/10W, SMD 0603 | R12 R106 R115 | R_0603_1608Metric | 3 | C144102 | YAGEO | AF0603FR-07330RL
Resistor, 33 Ohms, ±1%, 1/10W, SMD 0603 | R17 R18 R19 R20 R27 R28 R51 R52 R63 R64 R65 R66 R67 R68 R69 R70 R71 R72 R83 R84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 | R_0603_1608Metric | 27 | C108661 | YAGEO | RC0603FR-0733RL
Resistor, 47 kOhms, ±0.1%, 1/10W, SMD 0603 | R101 | R_0603_1608Metric | 1 | C2828645 | Viking Tech | AR03BTCX4702
Resistor, 5.62k Ohms, ±5%, 250 mW, SMD 0805 | R9 | R_0805_2012Metric_Pad1.20x1.40mm_HandSolder | 1 | C425493 | UNI-ROYAL(Uniroyal Elec) | TC0550D5621T5E
Resistor, 510 Ohms, ±0.1%, 1/10W, SMD 0603 | R25 | R_0603_1608Metric | 1 | C2828640 | Viking Tech | AR03BTCX5100
Resistor, 680 Ohms, ±1%, 1/10W, SMD 0603 | R11 | R_0603_1608Metric | 1 | C2097840 | YAGEO | AF0603FR-07680RL
Resistor, 82 kOhms, ±0.1%, 1/10W, SMD 0603 | R4 R7 R102 | R_0603_1608Metric | 3 | C728598 | YAGEO | RT0603BRD0782KL
Current Sense Resistor, 8 mOhms, ±1%, 2 W, SMD 2512 | R39 | R_2512_6332Metric_Pad1.40x3.35mm_HandSolder | 1 | C2440282 | JU YONG CHANG | AND2512EFR008
Unidirectional Transient Voltage Suppressor, 400W, 12Vrwm, 14.7 V Max. Breakdow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 | TV4 TV6 TV11 TV16 TV17 TV18 | D_SOD-123 | 6 | C456115 | Nexperia | PTVS12VS1UR,115
Unidirectional Transient Voltage Suppressor, 400W, 30Vrwm, 36.8 V Max. Breakdow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 | TV14 TV15 | D_SOD-123 | 2 | C553410 | Nexperia | PTVS30VS1UR,115
Unidirectional Transient Voltage Suppressor, 350W, 3.3 Vrwm, 6 V Max. Breakdown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 | TV3 TV20 | D_SOD-123 | 2 | C183521 | Nexperia | PTVS3V3S1UR,115
Unidirectional Transient Voltage Suppressor, 350W, 5 Vrwm, 7 V Max. Breakdown V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 | TV2 TV5 TV7 TV8 TV9 TV10 TV12 TV13 | D_SOD-123 | 8 | C478011 | Nexperia | PTVS5V0S1UR,115
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
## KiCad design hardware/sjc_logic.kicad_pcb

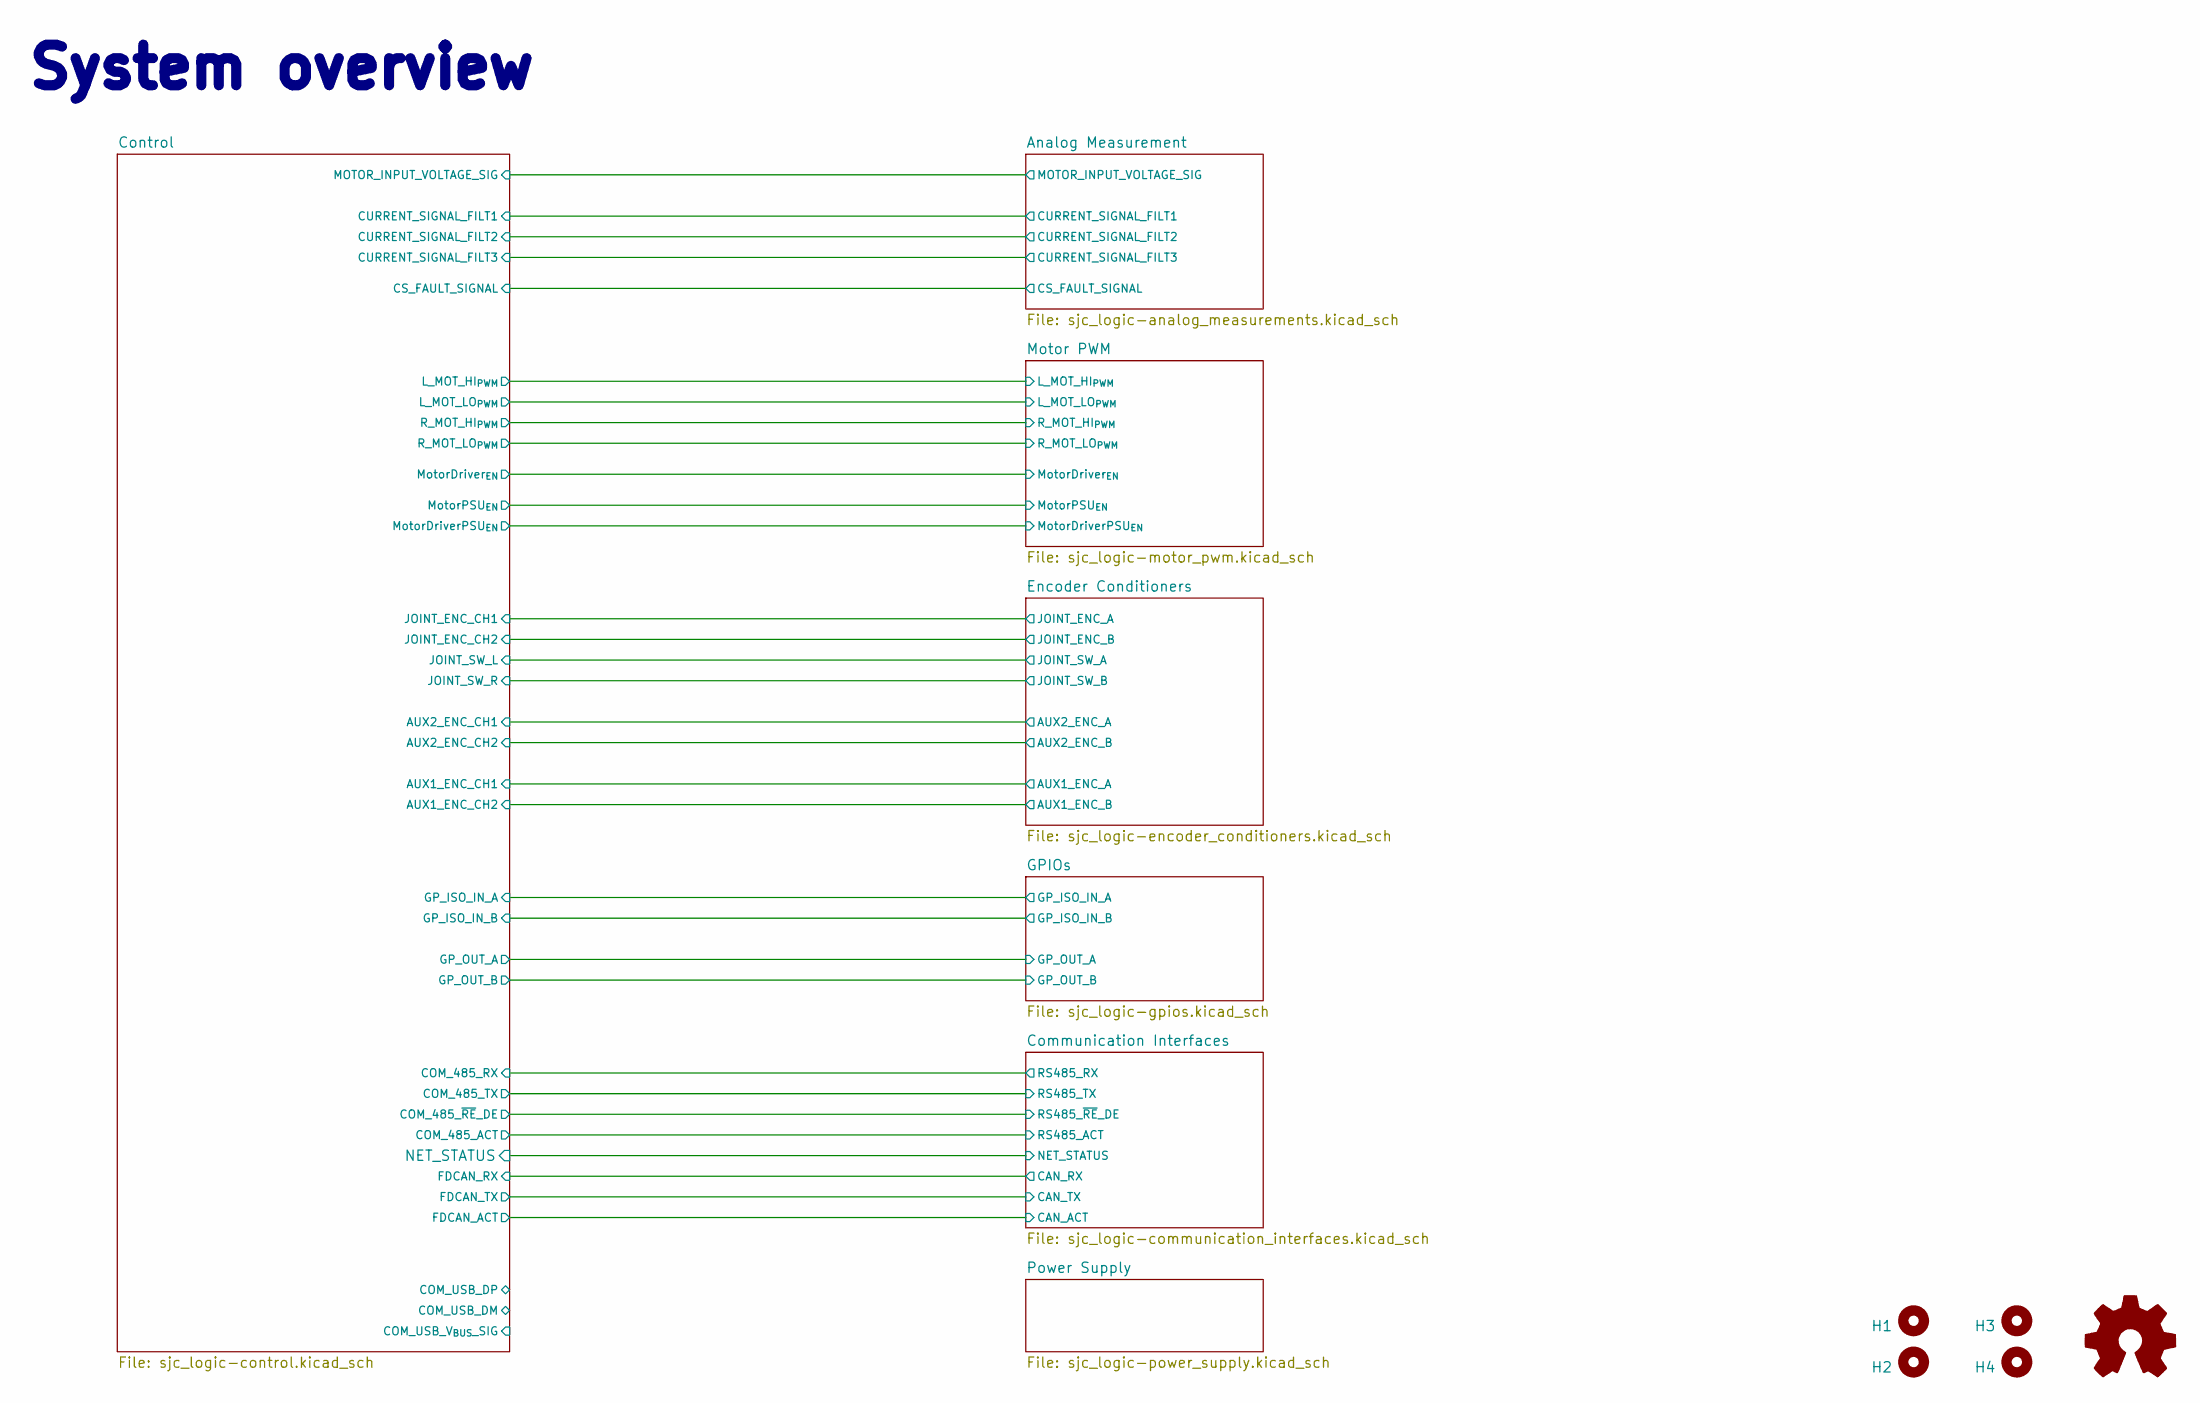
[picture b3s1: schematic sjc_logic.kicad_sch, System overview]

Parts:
H1, H2, H3, H4: MountingHole; MountingHole_3.2mm_M3_ISO7380
SYM1: Logo_Open_Hardware_Small; OSHW-Logo2_9.8x8mm_SilkScreen

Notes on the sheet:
System overview
